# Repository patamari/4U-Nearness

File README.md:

# 4U-Nearness
Port of Nearness by Jesper Särnesjö
CC BY-SA 4.0

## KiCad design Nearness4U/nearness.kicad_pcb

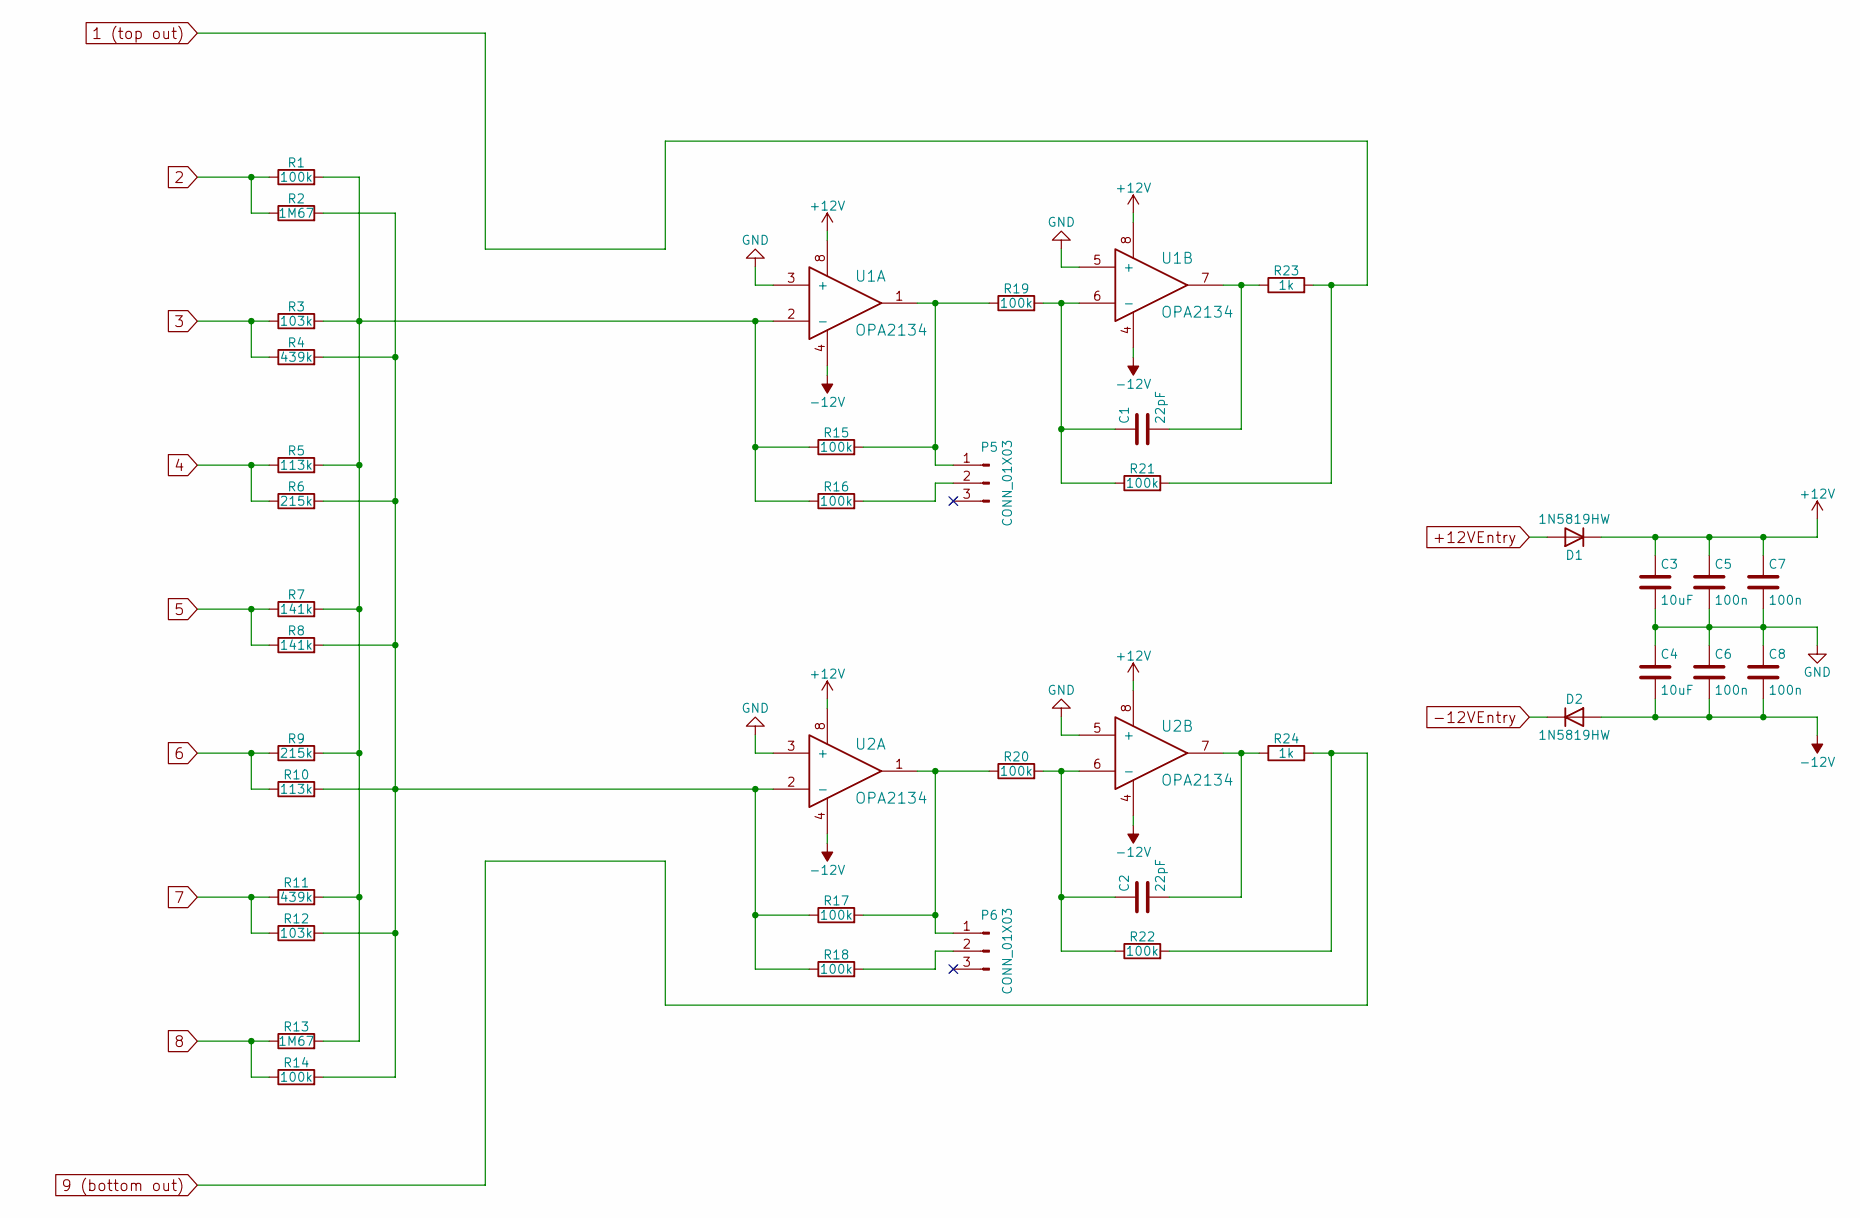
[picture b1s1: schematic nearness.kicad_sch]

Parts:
C1, C2: 22pF; 0603
C3, C4: 10uF; 0805
C5, C6, C7, C8: 100n; 0603
D1, D2: 1N5819HW; D_SOD-123
P5, P6: CONN_01X03; Pin_1x3
R1, R14, R15, R16, R17, R18, R19, R20, R21, R22: 100k; 0805
R2, R13: 1M67; 0805
R3, R12: 103k; 0805
R4, R11: 439k; 0805
R5, R10: 113k; 0805
R6, R9: 215k; 0805
R7, R8: 141k; 0805
R23, R24: 1k; 0805
U1, U2: OPA2134; SOIC-8_3.9x4.9mm_P1.27mm

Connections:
1 (top out): R21.2, R23.2
2: R1.1, R2.1
3: R3.1, R4.1
4: R5.1, R6.1
5: R7.1, R8.1
6: R9.1, R10.1
7: R11.1, R12.1
8: R13.1, R14.1
9 (bottom out): R22.2, R24.2
+12V: C3.1, C5.1, C7.1, D1.1 (K), U1.8, U2.8
+12VEntry: D1.2 (A)
-12V: C4.2, C6.2, C8.2, D2.2 (A), U1.4, U2.4
-12VEntry: D2.1 (K)
GND: C3.2, C4.1, C5.2, C6.1, C7.2, C8.1, U1.3 (+), U1.5 (+), U2.3 (+), U2.5 (+)
unnamed: C1.2, R23.1, U1.7
unnamed: C2.2, R24.1, U2.7
unnamed: P5.1, R15.2, R19.1, U1.1
unnamed: P5.2, R16.2
unnamed: P6.1, R17.2, R20.1, U2.1
unnamed: P6.2, R18.2
unnamed: R1.2, R3.2, R5.2, R7.2, R9.2, R11.2, R13.2, R15.1, R16.1, U1.2 (-)
unnamed: C1.1, R19.2, R21.1, U1.6 (-)
unnamed: R2.2, R4.2, R6.2, R8.2, R10.2, R12.2, R14.2, R17.1, R18.1, U2.2 (-)
unnamed: C2.1, R20.2, R22.1, U2.6 (-)
x: P5.3
y: P6.3

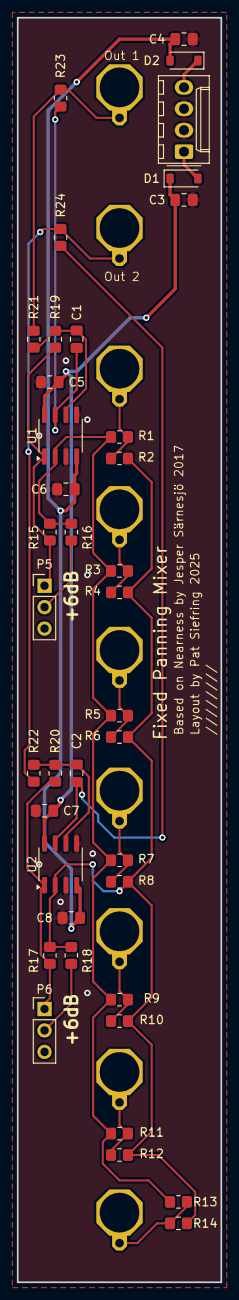
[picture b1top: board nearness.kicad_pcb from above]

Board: 2 copper layers, 24.1 x 149.9 mm, 38 parts (0 on the bottom side), 22 nets.
